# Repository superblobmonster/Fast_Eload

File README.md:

# Fast_Eload
Designed in KiCad 9.0.7 and FreeCAD 1.0.2

License: CC-BY-SA-4.0

## Design Specs
+ 10A/us slew rate
+ 15A RMS, 50A peak, 20A fuse
+ 100W (To be verified) average, peak power limited by FET SOA.
+ 100V input, 150V TVS protection, 250V+ rated parts.
+ 10V external power supply

## Design notes
+ Produce with 2oz copper
+ Fill and cap vias, or plate solid
+ Thinner PCB the better for thermal performance
+ Turn-off slew rates > 15A/us causes instability, root cause unknown

## Parts
+ CCA BOM: https://www.digikey.com/en/mylists/list/430F3M7L10

Additional parts/accessories:
+ Copper shim-stock: https://www.mcmaster.com/products/metals/copper-2~/shape~sheet/thickness~0-032/thickness~0-040/thickness~0-04/
+ TIM
+ Ring terminals
+ M3x4 screws
+ Amphenol MMCX to BNC: 095-850-207-006
+ Tektronix probe tip adaptor to BNC: 13036700
+ Ribbon cable assembly: 71600-308LF

## TODO and Notes
+ Validate thermal performance
+ Measure control bandwidth
+ Create control board with:
  + 10MS/s DAC
  + Slew rate limiting
  + V/I Monitoring: ADS7253?
    + Unregulation detection
    + SOA protections
  + Isolated input signal, 10MS/s ADC
  + Paralleling features, enable controls
+ Add temperature monitoring
+ Heatsink and interface design for equipment rack enclosure
+ Design a fully electrically isolated THT version with a SOT-227 FET

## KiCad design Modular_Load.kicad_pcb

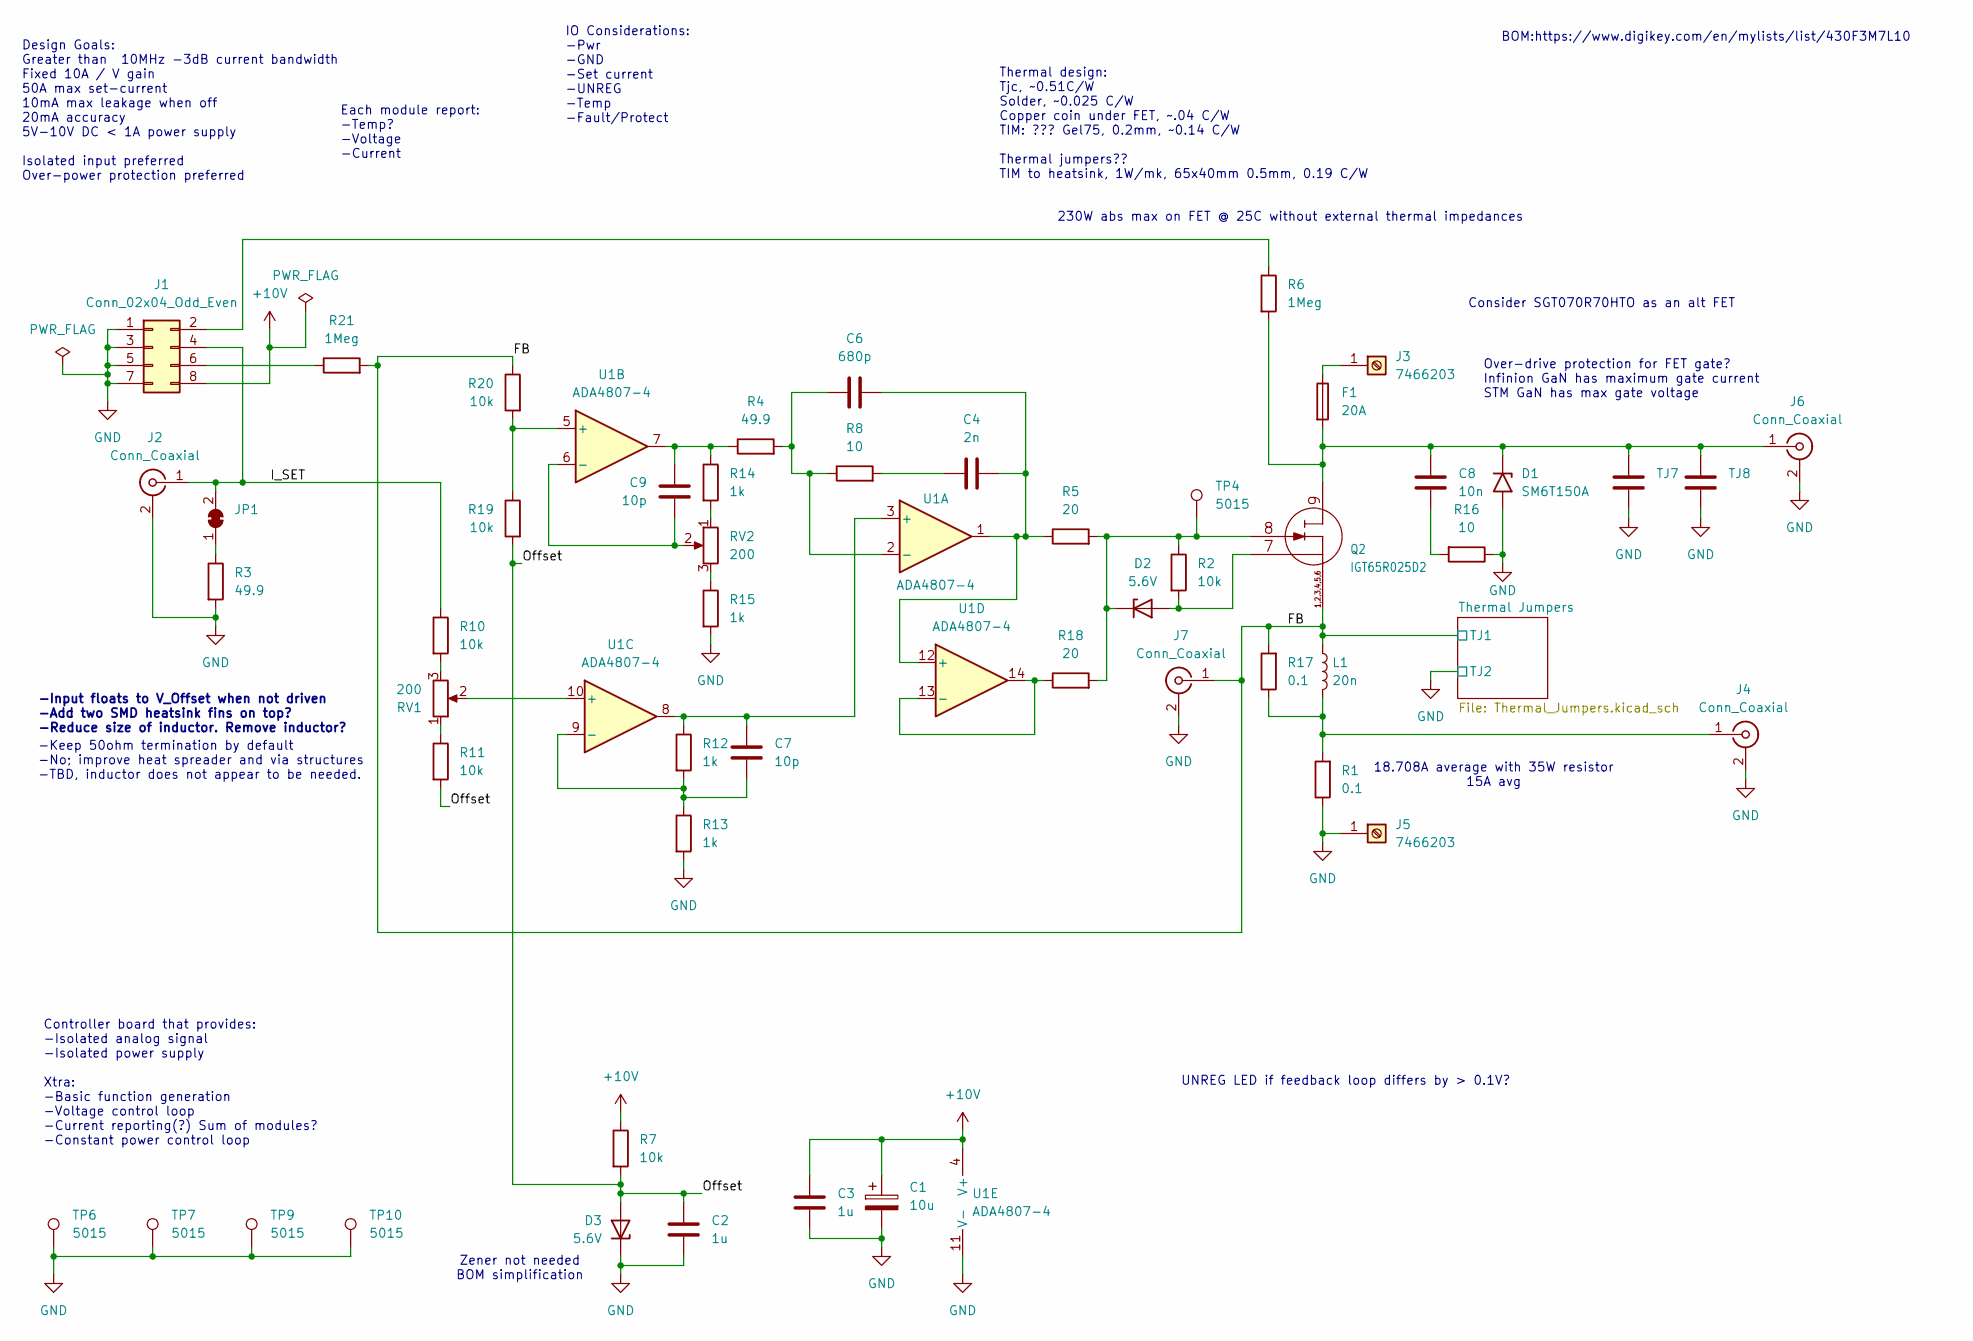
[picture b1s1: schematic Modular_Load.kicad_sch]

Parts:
C1: 10u; C_1206_3216Metric; PartNumber T491A106M016AT
C2, C3: 1u; C_0603_1608Metric; PartNumber C0603C105K4RACTU
C4: 2n; C_0603_1608Metric; PartNumber C0603C202J5GACTU
C6: 680p; C_0603_1608Metric; PartNumber C0603C681F5GACTU
C7, C9: 10p; C_0603_1608Metric; PartNumber C0603C100J5GACTU
C8: 10n; C_1206_3216Metric; PartNumber C1206X103JAGACAUTO
D1: SM6T150A; D_SMB; PartNumber SM6T150A
D2, D3: 5.6V; D_SOD-323_HandSoldering; PartNumber DDZ5V6BSF-7
F1: 20A; FUSE_0683G9200-01; PartNumber 0683G9200-01
J1: Conn_02x04_Odd_Even; PinHeader_2x04_P2.54mm_Vertical_SMD; PartNumber TSM-104-01-L-DV-P-TR
J2, J4, J6, J7: Conn_Coaxial; WR-MMCX_Wuerth_66012102111404_Vertical; PartNumber 66012102111404
J3, J5: 7466203; WP-SMBU_7466203; PartNumber 7466203
JP1: SolderJumper_2_Bridged; SolderJumper-2_P1.3mm_Bridged_RoundedPad1.0x1.5mm
L1: 20n; WE-ACHC_7449150023; PartNumber 7449152022
Q2: IGT65R025D2; IFX-PG-HSOF-8-12-V; PartNumber IGT65R025D2ATMA1
R1: 0.1; TO-263-2_TabPin1; PartNumber D2TO035CR1000FTE3
R2, R7, R10, R11, R19, R20: 10k; R_0603_1608Metric; PartNumber CRCW060310K0FKEA
R3, R4: 49.9; R_0603_1608Metric; PartNumber CRCW060349R9FKEA
R5, R18: 20; R_0603_1608Metric; PartNumber CRCW060320R0FKEA
R6, R21: 1Meg; R_0603_1608Metric; PartNumber CRCW06031M00FKEA
R8, R16: 10; R_0603_1608Metric; PartNumber CRCW060310R0FKEA
R12, R13, R14, R15: 1k; R_0603_1608Metric; PartNumber CRCW06031K00FKEA
R17: 0.1; R_0805_2012Metric; PartNumber RCWE0805R100FKEA
RV1, RV2: 200; Potentiometer_Bourns_3214W_Vertical; PartNumber 3214W-1-201E
TJ7, TJ8: THJP0612ABT1; R_0612_1632Metric_Pad1.18x3.40mm_HandSolder; PartNumber THJP0612AST1
TP4, TP6, TP7, TP9, TP10: 5015; TestPoint_Keystone_5015_Micro_Mini; PartNumber 5015
U1: ADA4807-4; TSSOP-14_4.4x5mm_P0.65mm; PartNumber ADA4807-4ARUZ-R7

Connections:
+10V: C1.1, C3.1, J1.8, R7.1, U1.4 (V+)
/FB: J7.1 (In), L1.1, Q2.1 (S1), Q2.2 (S2), Q2.3 (S3), Q2.4 (S4), Q2.5 (S5), Q2.6 (S6), R17.2, R20.1, R21.2; also elsewhere on the board
/I_SET: J1.4, J2.1 (In), JP1.2 (B), R10.1
/Offset: C2.1, D3.2 (A), R7.2, R11.2, R19.2
GND: C1.2, C2.2, C3.2, D1.2 (A2), D3.1 (K), J1.1, J1.3, J1.5, J1.7, J2.2 (Ext), J4.2 (Ext), J5.1, J6.2 (Ext), J7.2 (Ext), R1.1, R3.2, R13.2, R15.2, R16.1, TJ7.2, TJ8.2, TP6.1, TP7.1, TP9.1, TP10.1, U1.11 (V-); also elsewhere on the board
unnamed: C4.1, R8.2
unnamed: C8.2, R16.2
unnamed: C9.1, R4.1, R14.1, U1.7
unnamed: C8.1, D1.1 (A1), F1.2, J6.1 (In), Q2.9 (D), R6.2, TJ7.1, TJ8.1
unnamed: D2.2 (A), Q2.7 (SK), R2.2
unnamed: D2.1 (K), Q2.8 (G), R2.1, R5.2, R18.2, TP4.1
unnamed: J1.2, R6.1
unnamed: J1.6, R21.1
unnamed: F1.1, J3.1
unnamed: J4.1 (In), L1.2, R1.2, R17.1
unnamed: JP1.1 (A), R3.1
unnamed: R10.2, RV1.3
unnamed: R11.1, RV1.1
unnamed: R14.2, RV2.1
unnamed: R15.1, RV2.3
unnamed: C7.1, R12.1, U1.3 (+), U1.8
unnamed: C6.1, R4.2, R8.1, U1.2 (-)
unnamed: R19.1, R20.2, U1.5 (+)
unnamed: C9.2, RV2.2, U1.6 (-)
unnamed: RV1.2, U1.10 (+)
unnamed: C7.2, R12.2, R13.1, U1.9 (-)
unnamed: C4.2, C6.2, R5.1, U1.1, U1.12 (+)
unnamed: R18.1, U1.13 (-), U1.14

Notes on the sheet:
BOM:https://www.digikey.com/en/mylists/list/430F3M7L10
Thermal design: Tjc, ~0.51C/W Solder, ~0.025 C/W Copper coin under FET, ~.04 C/W TIM: ??? Gel75, 0.2mm, ~0.14 C/W Thermal jumpers?? TIM to heatsink, 1W/mk, 65x40mm 0.5mm, 0.19 C/W
230W abs max on FET @ 25C without external thermal impedances
Zener not needed BOM simplification
UNREG LED if feedback loop differs by > 0.1V?
Over-drive protection for FET gate? Infinion GaN has maximum gate current STM GaN has max gate voltage
18.708A average with 35W resistor 15A avg
Consider SGT070R70HTO as an alt FET
IO Considerations: -Pwr -GND -Set current -UNREG -Temp -Fault/Protect
-Input floats to V_Offset when not driven -Add two SMD heatsink fins on top? -Reduce size of inductor. Remove inductor?
Design Goals: Greater than 10MHz -3dB current bandwidth Fixed 10A / V gain 50A max set-current 10mA max leakage when off 20mA accuracy 5V-10V DC < 1A power supply Isolated input preferred Over-power protection preferred
Controller board that provides: -Isolated analog signal -Isolated power supply Xtra: -Basic function generation -Voltage control loop -Current reporting(?) Sum of modules? -Constant power control loop
-Keep 50ohm termination by default -No; improve heat spreader and via structures -TBD, inductor does not appear to be needed.
Each module report: -Temp? -Voltage -Current

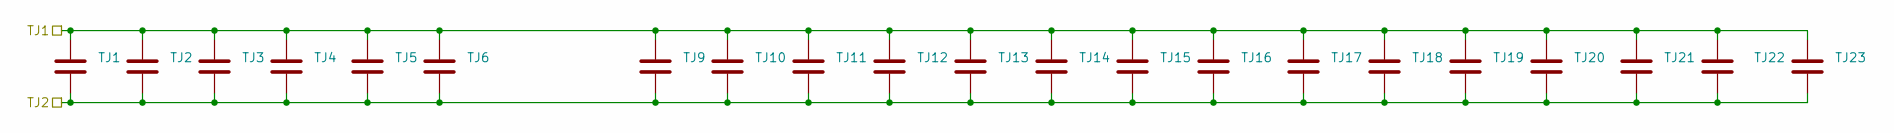
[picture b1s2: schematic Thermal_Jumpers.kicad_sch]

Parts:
TJ1, TJ2, TJ3, TJ4, TJ5, TJ6, TJ9, TJ10, TJ11, TJ12, TJ13, TJ14, TJ15, TJ16, TJ17, TJ18, TJ19, TJ20, TJ21, TJ22, TJ23: THJP0612ABT1; R_0612_1632Metric_Pad1.18x3.40mm_HandSolder; PartNumber THJP0612AST1

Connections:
/FB: TJ1.1, TJ2.1, TJ3.1, TJ4.1, TJ5.1, TJ6.1, TJ9.1, TJ10.1, TJ11.1, TJ12.1, TJ13.1, TJ14.1, TJ15.1, TJ16.1, TJ17.1, TJ18.1, TJ19.1, TJ20.1, TJ21.1, TJ22.1, TJ23.1; also elsewhere on the board
GND: TJ1.2, TJ2.2, TJ3.2, TJ4.2, TJ5.2, TJ6.2, TJ9.2, TJ10.2, TJ11.2, TJ12.2, TJ13.2, TJ14.2, TJ15.2, TJ16.2, TJ17.2, TJ18.2, TJ19.2, TJ20.2, TJ21.2, TJ22.2, TJ23.2; also elsewhere on the board

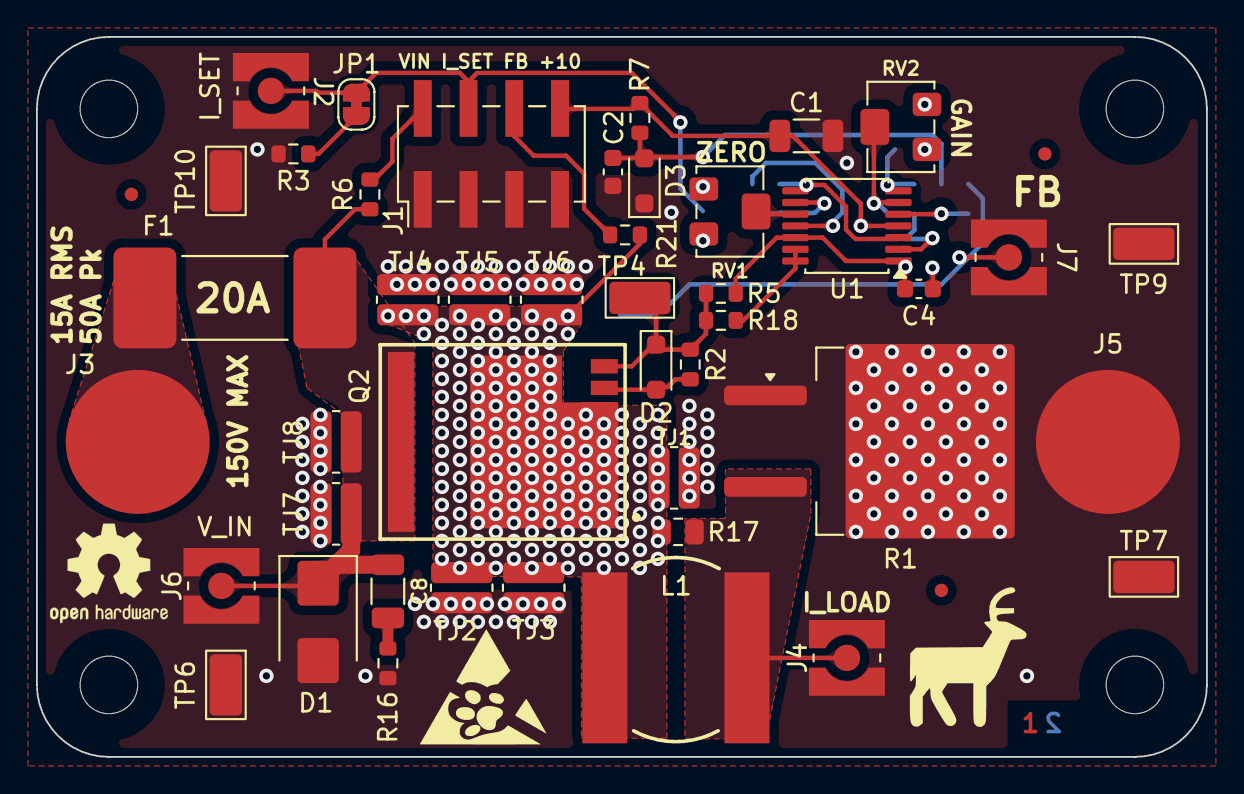
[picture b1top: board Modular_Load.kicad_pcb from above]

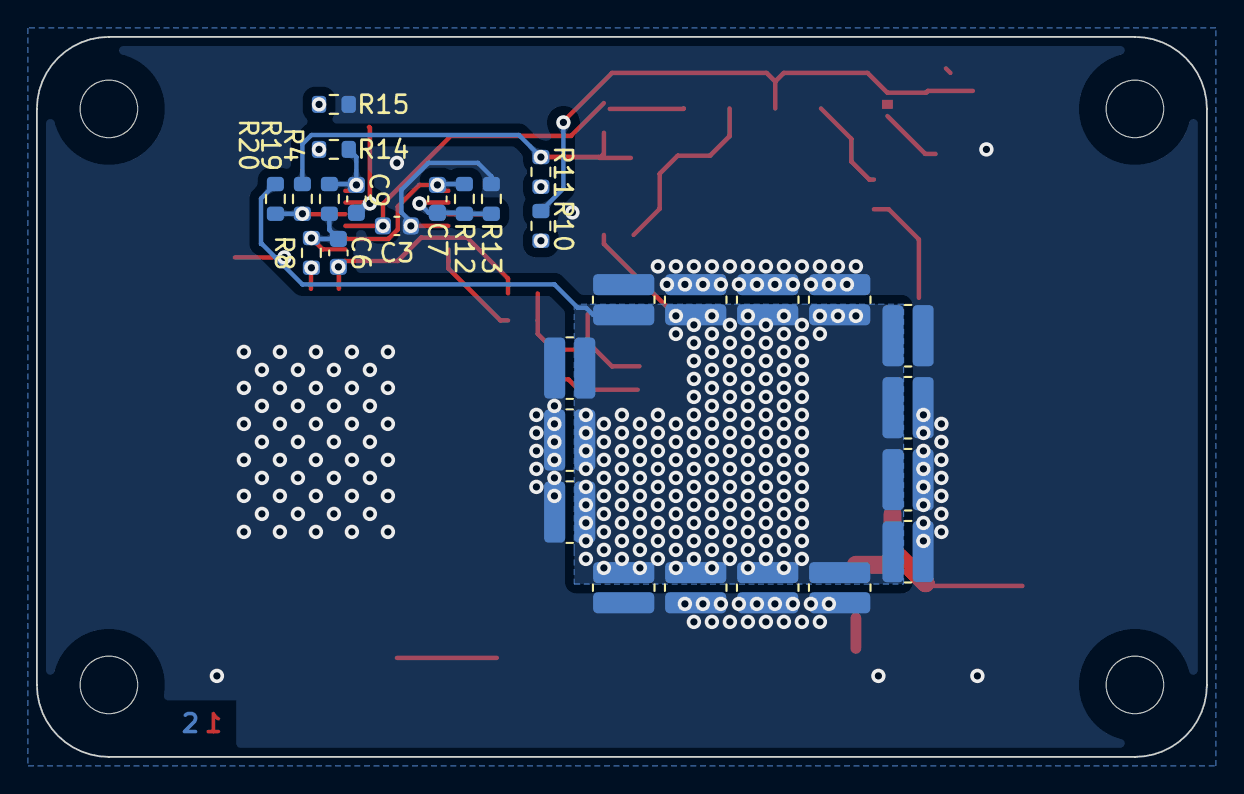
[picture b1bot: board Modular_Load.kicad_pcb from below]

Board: 2 copper layers, 65.0 x 40.0 mm, 84 parts (29 on the bottom side), 28 nets.

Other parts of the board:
FD1, FD2, FD3: Fiducial_0.75mm_Mask1.5mm
G1, G2: LOGO
G3: OSHW-Logo2_7.3x6mm_SilkScreen
H1, H2, H3, H4: MountingHole_3.2mm_M3_ISO7380
Layers: LayerMarker_2_3.81x2.54mm_TextH1mm_P1.27mm_Bottom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; LayerMarker_2_3.81x2.54mm_TextH1mm_P1.27mm_BottomMirrored

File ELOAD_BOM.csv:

"Reference","Value","Qty","PartNumber","DNP"
"C1","10u","1","T491A106M016AT",""
"C2,C3","1u","2","C0603C105K4RACTU",""
"C4","2n","1","C0603C202J5GACTU",""
"C6","680p","1","C0603C681F5GACTU",""
"C7,C9","10p","2","C0603C100J5GACTU",""
"C8","10n","1","C1206X103JAGACAUTO",""
"D1","SM6T150A","1","SM6T150A",""
"D2,D3","5.6V","2","DDZ5V6BSF-7",""
"F1","20A","1","0683G9200-01",""
"J1","Conn_02x04_Odd_Even","1","TSM-104-01-L-DV-P-TR",""
"J2,J4,J6,J7","Conn_Coaxial","4","66012102111404",""
"J3,J5","7466203","2","7466203",""
"L1","20n","1","7449152022",""
"Q2","IGT65R025D2","1","IGT65R025D2ATMA1",""
"R1","0.1","1","D2TO035CR1000FTE3",""
"R2,R7,R10,R11,R19,R20","10k","6","CRCW060310K0FKEA",""
"R3,R4","49.9","2","CRCW060349R9FKEA",""
"R5,R18","20","2","CRCW060320R0FKEA",""
"R6,R21","1Meg","2","CRCW06031M00FKEA",""
"R8,R16","10","2","CRCW060310R0FKEA",""
"R12,R13,R14,R15","1k","4","CRCW06031K00FKEA",""
"R17","0.1","1","RCWE0805R100FKEA",""
"RV1,RV2","200","2","3214W-1-201E",""
"TJ1,TJ2,TJ3,TJ4,TJ5,TJ6,TJ7,TJ8,TJ9,TJ10,TJ11,TJ12,TJ13,TJ14,TJ15,TJ16,TJ17,TJ18,TJ19,TJ20,TJ21,TJ22,TJ23","THJP0612ABT1","23","THJP0612AST1",""
"TP4,TP6,TP7,TP9,TP10","5015","5","5015",""
"U1","ADA4807-4","1","ADA4807-4ARUZ-R7",""

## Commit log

2025-12-27 Initial commit
    Fab files for v1
2025-12-27 Delete Modular_Load-backups directory
    Backups not necessary for rev control
2026-02-03 Add files via upload
    V2, added MMCX connectors, adjusted gain tuning, changed control connector, thermal layout update.
2026-02-16 V3 Update
    Thermal improvements, double-sided assembly, better reference stability
2026-02-16 Update README.md
    Links and part numbers
2026-02-16 Update README.md
    Additional design notes, added todo
2026-02-16 Update README.md
    ADC notes
2026-02-16 Update README.md
    Added photos
2026-02-16 Documentation update
    Additional documentation, updated BOM, schematic, and CCA drawings
2026-02-17 Update README.md
    Added CC-BY-SA-4.0
2026-02-23 Folder clean-up
2026-02-23 Added heatsink drawings, updated component 3D models
2026-02-23 Update README.md
    Updated board image
2026-02-23 FET 3D model, Fresh FAB export, updated README
2026-02-23 Updated Heatsink Models
2026-02-23 Removed backup file
2026-02-23 Added digikey BOM export
2026-02-23 Digikey BOM quantities update
2026-02-23 Assembly Doccumentation Updates
